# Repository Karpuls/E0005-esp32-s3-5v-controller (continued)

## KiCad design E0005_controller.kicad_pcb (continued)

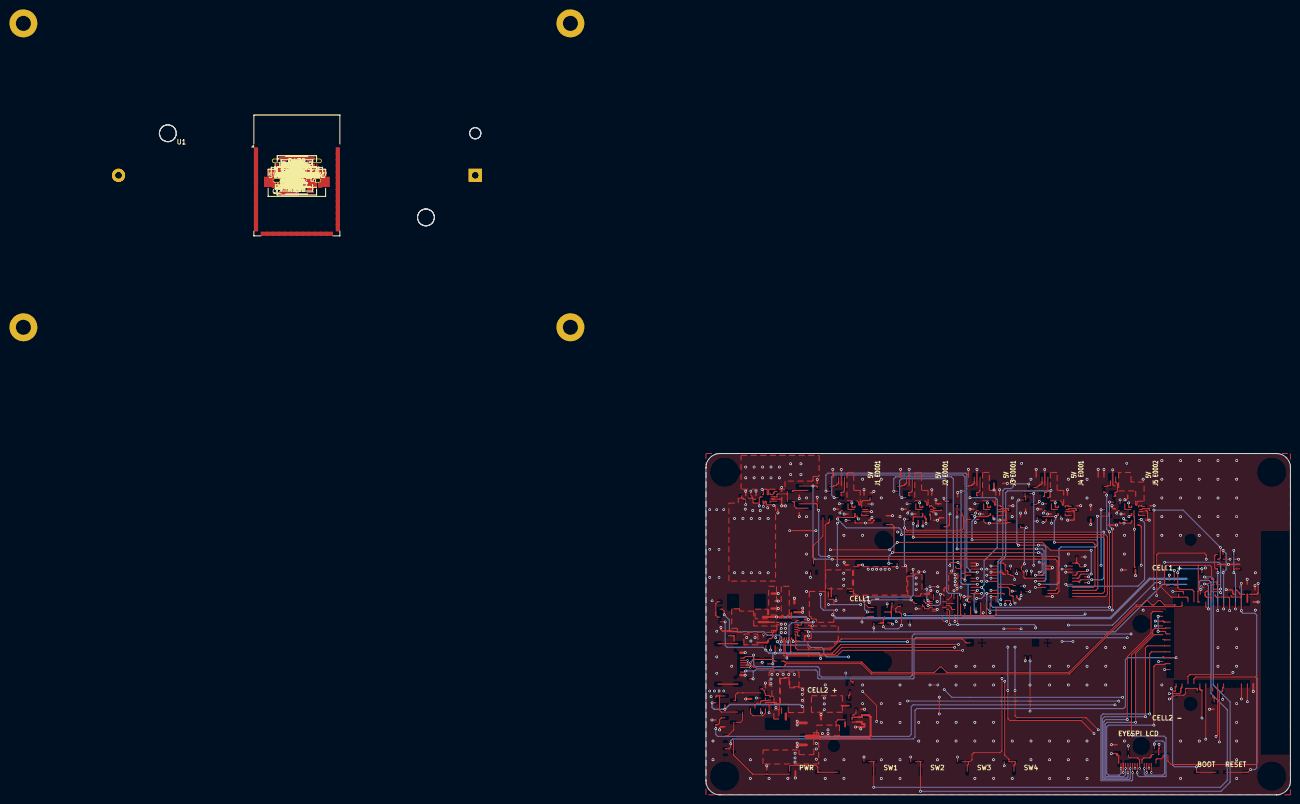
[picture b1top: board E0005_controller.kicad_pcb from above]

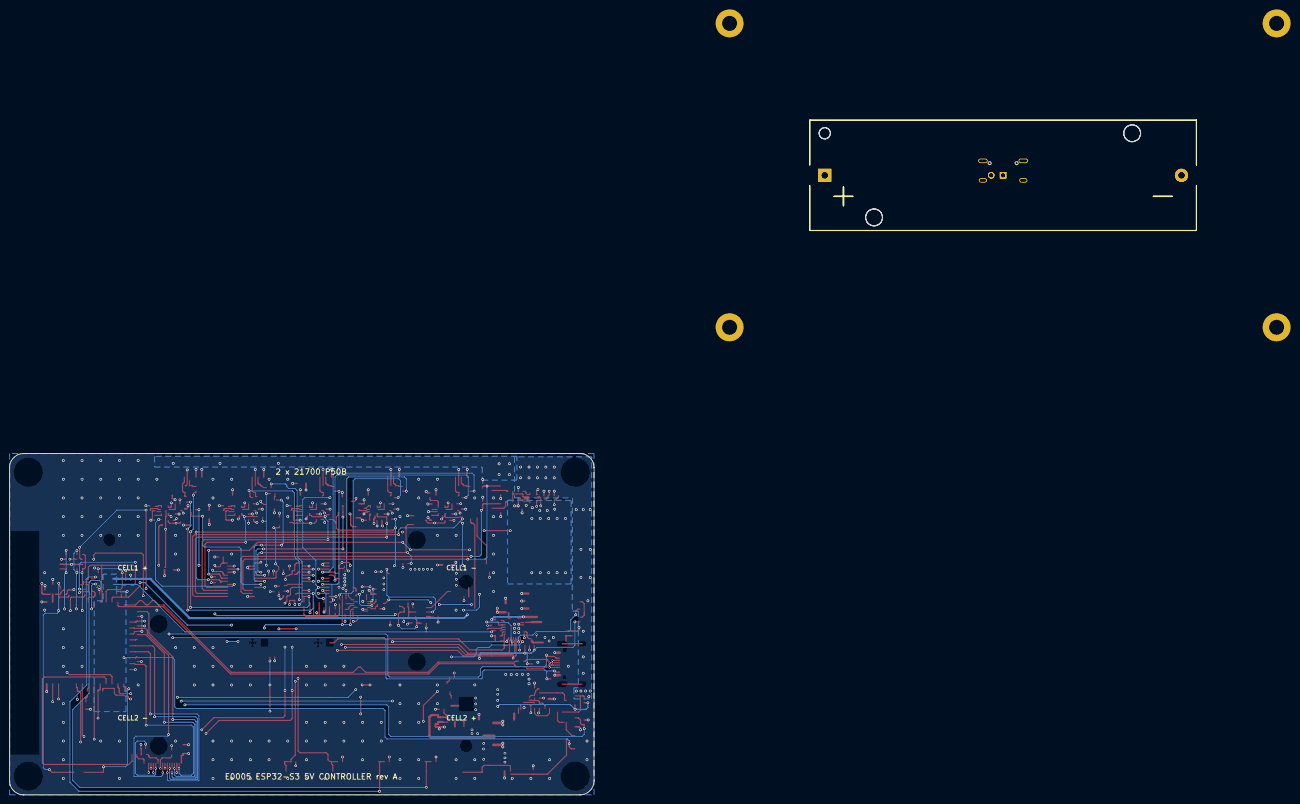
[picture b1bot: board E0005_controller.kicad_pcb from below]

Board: 4 copper layers, 125.0 x 73.0 mm, 270 parts (4 on the bottom side), 177 nets.

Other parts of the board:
OUT1: Holes_4xM3_125x73

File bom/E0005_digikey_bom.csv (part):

Supplier,Qty,QtyBasis,References,Value,Footprint,MPN,Manufacturer,SupplierPN,Stock,Lifecycle,UnitEUR,LeadWeeks,DNP,OwnerStock,Notes
DigiKey,2,schematic,BH1 BH2,Keystone 1121 + P50B,Keystone_1121_1x21700_THM,1121,Keystone Electronics,36-1121-ND,1372,Active,6.1,18,,no,E0003 data 2026-10-18. Mandatory P50B test fit before PCB order (PN/stock from DigiKey keyword search)
DigiKey,1,schematic,C1,4.7nF,C_0402_1005Metric,GRM155R71H472KA01J,Murata Electronics,490-8259-1-ND,143253,Active,0.09,17,,no,E0003 data 2026-10-18.
DigiKey,1,schematic,C2,1uF,C_0603_1608Metric,C1608X7R1H105K080AB,TDK,445-C1608X7R1H105K080ABCT-ND,26221,Active,0.2,24,,no,E0003 data 2026-10-18. Approved substitute; schematic field already updated
DigiKey,12,schematic,C8 C9 C18 C22 C42 C48 C51 C54 C57 C60 C71 C72,10uF,C_0805_2012Metric,TMK212BBJ106MG-T,Taiyo Yuden,587-6025-1-ND,237658,Active,0.18,23,,no,E0003 data 2026-10-18. Approved substitute; schematic field already updated
DigiKey,1,schematic,C11,47nF,C_0402_1005Metric,GRM155R71H473KE14D,Murata Electronics,490-10702-1-ND,636093,Active,0.09,17,,no,E0003 data 2026-10-18.
DigiKey,1,schematic,C20,4.7uF,C_0603_1608Metric,GRM188R61E475KE11D,Murata Electronics,490-7203-1-ND,713624,Active,0.21,17,,no,E0003 data 2026-10-18.
DigiKey,16,schematic,C23 C25 C26 C31 C36 C38 C39 C40 C41 C43 C44 C45 C65 C68 C73 C74,100nF,C_0402_1005Metric,GRM155R71H104KE14D,Murata Electronics,490-10700-1-ND,1430736,Active,0.09,17,,no,E0003 data 2026-10-18.
DigiKey,2,schematic,C24 C35,22uF,C_0805_2012Metric,CL21A226KQCLRNC,Samsung Electro-Mechanics,1276-6687-1-ND,167366,Active,0.15,61,,no,E0003 data 2026-10-18. Approved substitute; schematic field already updated
DigiKey,2,schematic,C32 C33,0.47uF,C_0402_1005Metric,GRM155R61A474KE15D,Murata Electronics,490-3264-1-ND,1604085,Active,0.11,17,,no,E0003 data 2026-10-18.
DigiKey,1,schematic,C37,1uF,C_0402_1005Metric,CL05A105KP5NNNC,Samsung Electro-Mechanics,1276-1076-1-ND,911254,Active,0.09,61,,no,E0003 data 2026-10-18.
DigiKey,6,schematic,C46 C49 C52 C55 C58 C66,1.8nF,C_0402_1005Metric,C0402C182K5RACTU,KEMET,399-C0402C182K5RACTUCT-ND,9731,Active,0.44,17,,no,E0003 data 2026-10-18.
DigiKey,6,schematic,C47 C50 C53 C56 C59 C67,22nF,C_0402_1005Metric,GRM155R71H223KA12D,Murata Electronics,490-3884-1-ND,244845,Active,0.1,17,,no,E0003 data 2026-10-18.
DigiKey,2,schematic,C63 C64,1nF,C_0402_1005Metric,GRM155R71H102KA01D,Murata Electronics,490-1303-1-ND,4189153,Active,0.1,21,,no,E0003 data 2026-10-18.
DigiKey,4,schematic,C69 C70 C75 C76,47uF,C_1210_3225Metric,CL32A476KOJNNNE,Samsung Electro-Mechanics,1276-3376-1-ND,256510,Active,0.76,61,,no,E0003 data 2026-10-18. Approved substitute; schematic field already updated
DigiKey,1,schematic,C79,100pF,C_0402_1005Metric,GRM1555C1H101JA01D,Murata Electronics,490-5922-1-ND,107905,Active,0.11 USD @1,,,no,"NEW in E0005, DigiKey checked 2026-10-27. 100 pF C0G (TR 490-5922-2-ND)"
DigiKey,1,schematic,D1,SMF9.0A,D_SOD-123F,SMF9.0A,Littelfuse Inc.,F5755CT-ND,2437,Active,0.47,20,,no,E0003 data 2026-10-18.
DigiKey,1,schematic,D2,amber,LED_0603_1608Metric,LTST-C191KSKT,Lite-On Inc.,160-1448-1-ND,852866,Active,0.14,14,,no,E0003 data 2026-10-18. 590 nm yellow-amber
DigiKey,6,schematic,D3 D5 D7 D8 D13 D14,BAT54W,SOT-323_SC-70,"BAT54W,135",Nexperia USA Inc.,1727-1869-1-ND,26776,Active,0.17,30,,no,E0003 data 2026-10-18. Approved substitute; schematic field already updated
DigiKey,2,schematic,D4 D6,red,LED_0603_1608Metric,LTST-C191KRKT,Lite-On Inc.,160-1447-1-ND,1445960,Active,0.13,14,,no,E0003 data 2026-10-18.
DigiKey,1,schematic,D11,green,LED_0603_1608Metric,LTST-C191KGKT,Lite-On Inc.,160-1446-1-ND,2812317,Active,0.13,14,,no,E0003 data 2026-10-18.
DigiKey,1,schematic,D12,TPD1E10B09,D_0402_1005Metric,TPD1E10B09DPYR,Texas Instruments,296-30405-1-ND,48491,Active,0.65 USD @1,,,no,"NEW in E0005, DigiKey checked 2026-10-27. 9 V bidirectional ESD, X1SON-2 0402 (TR 296-30405-2-ND)"
DigiKey,4,schematic,D15 D16 D17 D18,PESD5V0L1UL,D_SOD-882,"PESD5V0L1UL,315",Nexperia USA Inc.,1727-4193-1-ND,18740,Active,0.22,30,,no,E0003 data 2026-10-18.
DigiKey,5,schematic,D19 D21 D23 D25 D27,SMF5.0A,D_SOD-123F,SMF5.0A,Littelfuse Inc.,F5748CT-ND,21423,Active,0.50 USD @1,,,no,"NEW in E0005, DigiKey checked 2026-10-27. common part E0001/E0002"
DigiKey,5,schematic,D20 D22 D24 D26 D28,TPD2E2U06DRL,SOT-553,TPD2E2U06DRLR,Texas Instruments,296-38361-1-ND,74139,Active,0.97,12,,no,"E0003 data 2026-10-18. Spec: <=1 pF/line, VRWM>=3.6V (0.5 pF typ)"
DigiKey,1,schematic,F1,10A T,Fuse_Littelfuse-NANO2-451_453,0452010.MRL,Littelfuse Inc.,18-0452010.MRLCT-ND,2932,Active,3.78,19,,no,"E0003 data 2026-10-18. Nano2 SMF, 125 VAC/VDC"
LCSC,4,schematic,J1 J2 J3 J4,SM04B-GHS-TB,JST_GH_SM04B-GHS-TB_1x04-1MP_P1.25mm_Horizontal,SM04B-GHS-TB,JST,LCSC C189895 (SM04B-GHS-TB(LF)(SN)),2305 (LCSC),Active,0.31 USD @5 (LCSC),,,yes,E0003 data 2026-10-18. DigiKey stock 0 on 2026-10-18 (DigiKey PN 455-1566-1-ND); LCSC min order 5 BOM EXCEPTION (not DigiKey)
DigiKey,1,schematic,J5,SM06B-GHS-TB,JST_GH_SM06B-GHS-TB_1x06-1MP_P1.25mm_Horizontal,SM06B-GHS-TB(LF)(SN),JST Sales America Inc.,455-1568-1-ND,160364,Active,0.43,16,,yes,E0003 data 2026-10-18.
LCSC,5,schematic,J6 J7 J8 J9 J12,SM02B-GHS-TB,JST_GH_SM02B-GHS-TB_1x02-1MP_P1.25mm_Horizontal,SM02B-GHS-TB,JST,LCSC C189893 (SM02B-GHS-TB(LF)(SN)),29910 (LCSC),Active,0.51 USD @5 (LCSC),,,no,E0003 data 2026-10-18. DigiKey stock 0 on 2026-10-18 (DigiKey PN 455-1564-1-ND); LCSC min order 5 BOM EXCEPTION (not DigiKey)
DigiKey,1,schematic,J10,FH12-18S-0.5SH,Hirose_FH12-18S-0.5SH_1x18-1MP_P0.50mm_Horizontal,FH12-18S-0.5SH(55),Hirose Electric Co Ltd,HFJ118CT-ND,5602,Active,2.08,16,,no,E0003 data 2026-10-18.
DigiKey,1,schematic,J11,USB4105-GF-A,USB_C_Receptacle_GCT_USB4105-xx-A_16P_TopMnt_Horizontal,USB4105-GF-A,GCT,2073-USB4105-GF-ACT-ND,97080,Active,0.7,7,,no,E0003 data 2026-10-18.
DigiKey,1,schematic,L1,3.3uH,L_Vishay_IHLP-3232,IHLP3232DZER3R3M11,Vishay Dale,541-1352-1-ND,5904,Active,1.29 USD @1,,,no,"NEW in E0005, DigiKey checked 2026-10-27. 3.3 uH 10.5 A rated / 9.7 A sat, 14.9 mOhm max, 8.64 x 8.18 x 4.0 mm; TPS56637 datasheet part (TR 541-1352-2-ND)"
DigiKey,1,schematic,L2,1uH,L_Vishay_IHLP-2525,IHLP2525CZER1R0M01,Vishay Dale,541-1006-1-ND,38987,Active,1.11 USD @1,,,no,"NEW in E0005, DigiKey checked 2026-10-27. 1 uH 11 A rated / 22 A sat, 10 mOhm max (TR 541-1006-2-ND)"
DigiKey,1,schematic,L3,2.2uH,L_1008_2520Metric,DFE252012PD-2R2M=P2,Murata Electronics,490-DFE252012PD-2R2M=P2CT-ND,8950,Active,0.36,21,,no,E0003 data 2026-10-18. Per TPS629210 datasheet table 9-4
DigiKey,2,schematic,Q1 Q2,PSMN2R0-30YLDX,LFPAK56,PSMN2R0-30YLDX,Nexperia USA Inc.,1727-2218-1-ND,3965,Active,1.29,16,,no,"E0003 data 2026-10-18. With ~5 mR total the S-8252 OC trip is ~30 A, F1 10 A is the real limit (notes.md)"
DigiKey,8,schematic,Q3 Q4 Q5 Q6 Q7 Q11 Q12 Q14,2N7002,SOT-23,2N7002-7-F,Diodes Incorporated,2N7002-FDICT-ND,431766,Active,0.18,36,,no,E0003 data 2026-10-18. 5 port EN + OV2 + spare + BAL_EN (Q10)
DigiKey,1,schematic,Q13,AO3401A,SOT-23,AO3401A,Alpha & Omega Semiconductor Inc.,785-1001-1-ND,321804,Active,0.52 USD @1,,,no,"NEW in E0005, DigiKey checked 2026-10-27. common part (E0001/E0002); -30 V, VGS +-12 V, Vth -1.3 V max"
DigiKey,1,schematic,R1,1M,R_0402_1005Metric,RC0402FR-071ML,YAGEO,311-1.00MLRCT-ND,961162,Active,0.09,22,,no,E0003 data 2026-10-18.
DigiKey,2,schematic,R2 R3,0R,R_0402_1005Metric,RC0402JR-070RL,YAGEO,311-0.0JRCT-ND,1032165,Active,0.09,22,,no,E0003 data 2026-10-18.
DigiKey,1,schematic,R10,5.23k 1%,R_0402_1005Metric,RC0402FR-075K23L,YAGEO,YAG3195CT-ND,39950,Active,0.09,22,,no,E0003 data 2026-10-18.
DigiKey,1,schematic,R11,30.1k 1%,R_0402_1005Metric,RC0402FR-0730K1L,YAGEO,311-30.1KLRCT-ND,12740,Active,0.09,22,,no,E0003 data 2026-10-18.
DigiKey,30,schematic,R12 R35 R36 R37 R38 R40 R41 R42 R43 R57 R58 R59 R62 R63 R76 R77 R78 R79 R81 R83 R85 R87 R89 R90 R92 R93 R131 R132 R144 R149,10k,R_0402_1005Metric,RC0402FR-0710KL,YAGEO,311-10.0KLRCT-ND,10874291,Active,0.09,22,,no,E0003 data 2026-10-18.
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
